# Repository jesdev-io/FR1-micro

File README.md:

# FR1-micro - Waveshare ESP32-S3-Touch-LCD-1.47 with libFRX

This project demonstrates using libFRX with the Waveshare ESP32-S3-Touch-LCD-1.47 board.

## Features

- **SD Card Access**: Write and read files using libFRX's SD card module
- **Audio Support**: Configured for the onboard MEMS microphone and DAC
- **I2C Support**: Ready for I2C device communication
- **jescore Integration**: Full command-line interface support

## Setup

### Prerequisites

1. Install PlatformIO
2. Clone this repository
3. Ensure libFRX is accessible (configured as a git dependency)

### Building and Uploading

```bash
cd FR1-micro
pio run -t upload
```

### Monitoring

```bash
pio device monitor
```

## Demo Program

The demo in `src/main.cpp` shows basic libFRX SD card operations:
- Initialize jescore and SD card
- Create/write/read/delete files
- List directory contents
- Proper error handling and cleanup

## Configuration

See `PIN_DEFS.md` for detailed pin definitions and `platformio.ini` for build configuration.

## Board Specifications

- **MCU**: ESP32-S3
- **Flash**: 16MB
- **PSRAM**: 8MB
- **Display**: 1.47" 172x320 RGB LCD with touch
- **SD Card**: SDMMC interface
- **Audio**: MEMS microphone + DAC
- **Connectivity**: WiFi + Bluetooth 5.0

## Troubleshooting

- **SD Card**: Ensure proper insertion, FAT32 format, check connections
- **Audio**: Verify I2S connections and sample rate settings
- **Compilation**: Check `platformio.ini` for correct module enables and pin definitions

## License

This project is licensed under the MIT License. See the LICENSE file for details.

## Contributing

Contributions are welcome! Please open issues or pull requests for any improvements or bug fixes.

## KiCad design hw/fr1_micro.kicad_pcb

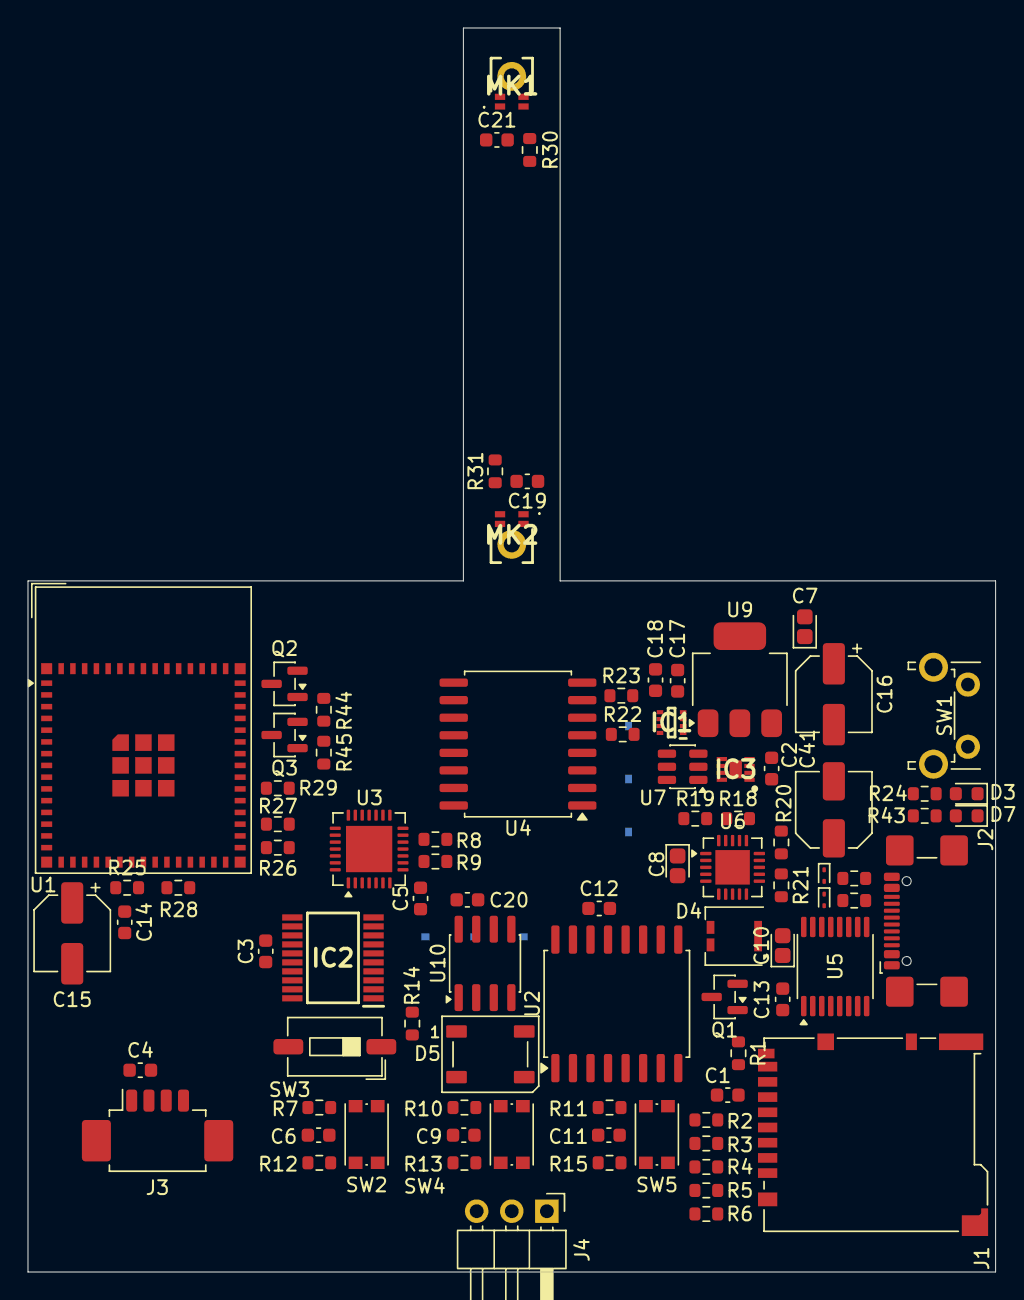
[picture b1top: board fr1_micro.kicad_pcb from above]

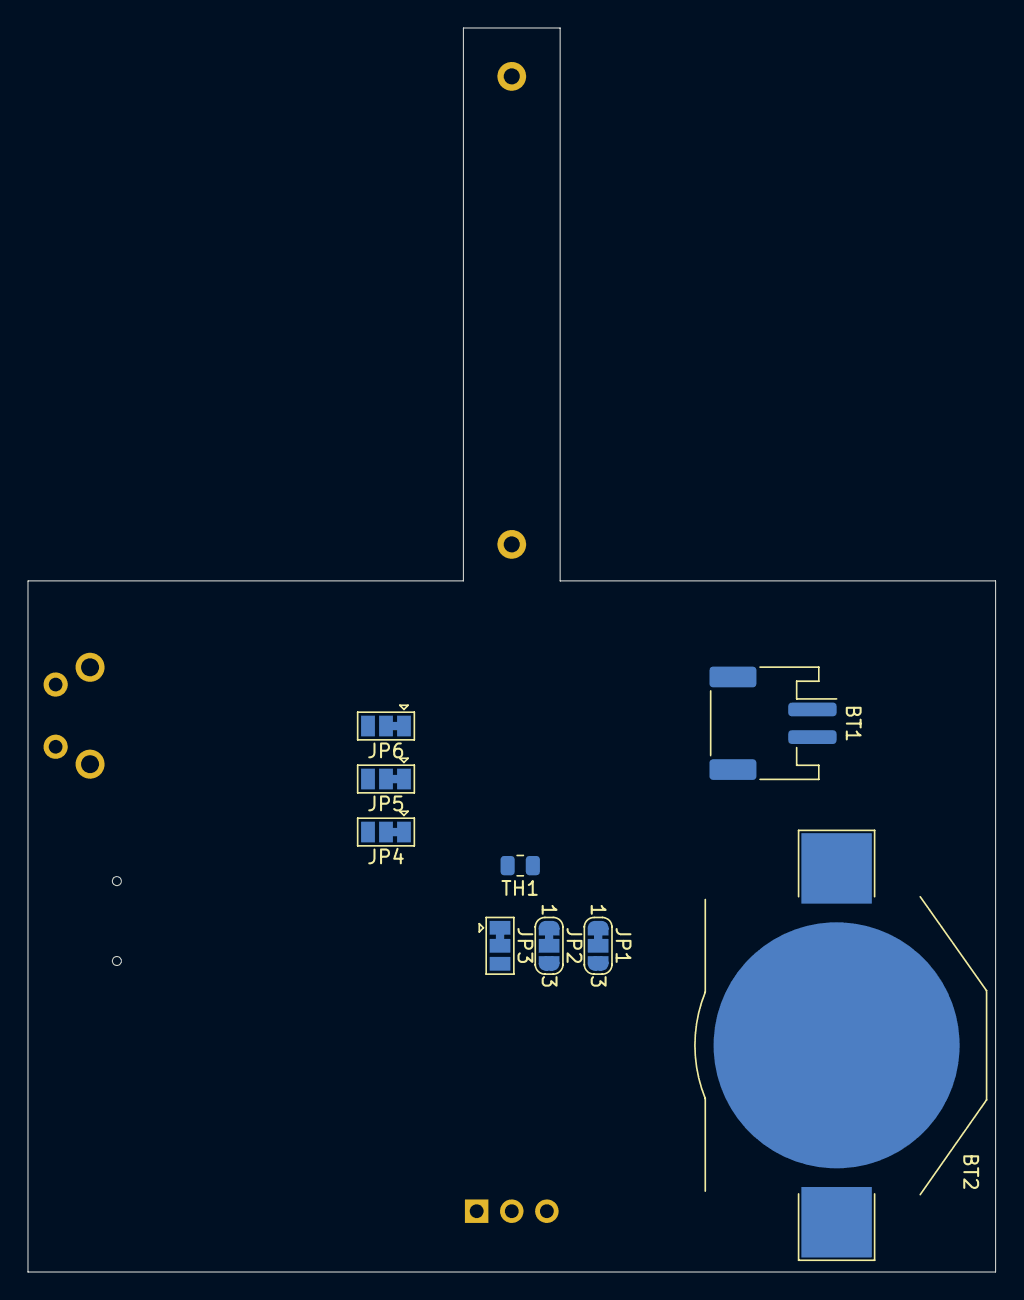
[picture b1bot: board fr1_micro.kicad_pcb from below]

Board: 4 copper layers, 70.0 x 90.0 mm, 97 parts (9 on the bottom side), 74 nets, no tracks yet.

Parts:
BT1: Battery_Cell; JST_PH_S2B-PH-SM4-TB_1x02-1MP_P2.00mm_Horizontal
BT2: Battery_Cell; BatteryHolder_Keystone_3002_1x2032
C1, C2, C3, C4, C5, C6, C9, C11, C12, C14, C19, C20, C21: 100n; C_0603_1608Metric
C7: 22u; CP_EIA-1608-08_AVX-J
C8: 4u7; CP_EIA-1608-08_AVX-J
C10: 10u; CP_EIA-1608-08_AVX-J
C13: 1µ; C_0603_1608Metric
C15: 47u; CP_Elec_5x5.4
C16: 4µ7; CP_Elec_5x5.4
C17: 100p; C_0603_1608Metric
C18: 6.8nF; C_0603_1608Metric
C41: 4u7; C_Elec_5x5.4
D1, D2: ESD9B3.3ST5G; D_SOD-923
D3: RED; D_0603_1608Metric
D4: ZEN056V230A16LS; Littelfuse_PolyZen-LS
D5: WS2812B; LED_WS2812B_PLCC4_5.0x5.0mm_P3.2mm
D7: GREEN; D_0603_1608Metric
IC1: TPS3424A11C13ADRLR; SOTFL50P160X60-8N
IC2: ADG5434BRUZ; SOP65P640X120-20N
IC3: MAX17048G+T10; SON50P200X200X80-9N-D
J1: Micro_SD_Card_Det1; microSD_HC_Hirose_DM3BT-DSF-PEJS
J2: USB_C_Receptacle; USB_C_Receptacle_GCT_USB4110
J3: Conn_01x04_Pin; Molex_PicoBlade_53261-0471_1x04-1MP_P1.25mm_Horizontal
J4: Conn_01x03_Pin; PinHeader_1x03_P2.54mm_Horizontal
JP1, JP2: SolderJumper_3_Bridged12; SolderJumper-3_P1.3mm_Bridged12_RoundedPad1.0x1.5mm_NumberL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
JP3, JP4, JP5, JP6: SolderJumper_3_Bridged12; SolderJumper-3_P1.3mm_Bridged12_Pad1.0x1.5mm
MK1, MK2: IM72D128V01XTMA1
Q1: AO3400A; SOT-23
Q2, Q3: BC847; SOT-23
R1, R2, R3, R4, R5, R6, R7, R8, R10, R11, R14, R22, R23, R44, R45: 10k; R_0603_1608Metric
R9: 1k; R_0603_1608Metric
R12, R13, R15: 100; R_0603_1608Metric
R16, R17: 5k1; R_0603_1608Metric
R18: 330k; R_0603_1608Metric
R19: 110k; R_0603_1608Metric
R20: 2k; R_0603_1608Metric
R21: 20k; R_0603_1608Metric
R24, R43: 470; R_0603_1608Metric
R25, R26, R27, R30, R31: 63; R_0603_1608Metric
R28, R29: 4k7; R_0603_1608Metric
SW1: SW_Push; SW_Tactile_SPST_Angled_PTS645Vx31-2LFS
SW2, SW4, SW5: SW_Push; SW_Push_1P1T_NO_CK_KMR2
SW3: SW_DIP_x01; SW_DIP_SPSTx01_Slide_6.7x4.1mm_W6.73mm_P2.54mm_LowProfile_J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
TH1: Thermistor_NTC 10k; R_0805_2012Metric
U1: ESP32-S3-MINI-1; ESP32-S2-MINI-1
U2: DS3231M; SOIC-16W_7.5x10.3mm_P1.27mm
U3: CP2102N-Axx-xQFN28; QFN-28-1EP_5x5mm_P0.5mm_EP3.35x3.35mm
U4: PCF8574AT; SOIC-16W_7.5x10.3mm_P1.27mm
U5: IP2721; TSSOP-16_4.4x5mm_P0.65mm
U6: MCP73871; QFN-20-1EP_4x4mm_P0.5mm_EP2.5x2.5mm
U7: TPS22917DBV; SOT-23-6
U9: AMS1117-3.3; SOT-223-3_TabPin2
U10: 24LC256; SOIC-8_3.9x4.9mm_P1.27mm

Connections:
+3.3V: C1.1, C3.1, C4.1, C5.2, C7.1, C14.1, C15.1, C19.1, C20.1, C21.1, C41.1, D5.1 (VDD), IC2.16 (VDD), J1.4 (VDD), J3.1, JP1.1 (A), JP2.1 (A), JP3.1 (A), JP4.1 (A), JP5.1 (A), JP6.1 (A), MK1.2 (VDD), MK2.2 (VDD), MK2.4 (SELECT), R1.1, R2.1, R3.1, R4.1, R5.1, R6.1, R7.2, R9.1, R10.2, R11.2, R14.2, R22.2, R23.2, R28.2, R29.2, U1.3 (3V3), U2.2 (VCC), U3.6 (VDD), U3.7 (VREGIN), U4.16 (VDD), U9.2 (VO), U10.8 (VCC)
/comms/DTR: Q3.2 (E), R44.1, U3.28 (~DTR)
/comms/RTS: Q2.2 (E), R45.1, U3.24 (~RTS)
/comms/USB_UART_D+: IC2.2 (S1A), J4.1, U3.4 (D+)
/comms/USB_UART_D-: IC2.9 (S2A), J4.2, U3.5 (D-)
/power/5V_ON: C8.1, IC1.3 (VDD), U6.1 (OUT), U6.20 (OUT), U7.1 (VIN)
/power/5V_PD: D4.3 (VOUT), R18.2, R24.1, R43.1, U6.4 (PROG2), U6.17 (CE), U6.18 (IN), U6.19 (IN)
/power/SWITCH_PIN: IC1.1 (PB), SW1.1
/power/TH: TH1.1, U6.5 (THERM)
/power/VBATT: BT1.1 (+), C2.1, C16.2, IC3.2 (CELL), IC3.3 (VDD), U6.14 (V_{BAT}), U6.15 (V_{BAT}), U6.16 (V_{BAT_SENSE})
BOOT: Q3.3 (C), U1.4 (IO0)
CC1: J2.A5 (CC1), R16.2, U5.13 (CC1)
CC2: J2.B5 (CC2), R17.2, U5.12 (CC2)
COMMS_UART_RX: U1.39 (TXD0), U3.25 (RXD)
COMMS_UART_TX: U1.40 (RXD0), U3.26 (TXD)
EN: Q2.3 (C), U1.45 (EN)
GNDD: BT1.2 (-), BT2.2 (-), C1.2, C2.2, C3.2, C4.2, C5.1, C6.2, C7.2, C8.2, C9.2, C10.2, C11.2, C12.2, C13.1, C14.2, C15.2, C16.1, C17.1, C18.1, C19.2, C20.2, C21.2, C41.2, D1.1 (A1), D2.1 (A1), D4.2 (GND), D5.3 (VSS), IC1.2 (GND), IC2.5 (VSS), IC2.6 (GND), IC2.11 (IN3), IC2.12 (S3A), IC2.13 (D3), IC2.14 (S3B), IC2.17 (S4B), IC2.18 (D4), IC2.19 (S4A), IC2.20 (IN4), IC3.1 (CTG), IC3.4 (GND), IC3.6 (QSTRT), IC3.9 (EP), J1.6 (VSS), J1.10 (SHIELD), J2.A1 (GND), J2.A12 (GND), J2.B1 (GND), J2.B12 (GND), J3.2, J4.3, JP1.3 (B), JP2.3 (B), JP3.3 (B), JP4.3 (B), JP5.3 (B), JP6.3 (B), MK1.4 (SELECT), MK1.5 (GND), MK2.5 (GND), R8.2, R16.1, R17.1, R19.1, R20.2, R21.2, SW1.2, SW2.1, SW3.2, SW4.1, SW5.1, TH1.2, U1.1 (GND), U1.2 (GND), U1.42 (GND), U1.43 (GND), U1.46 (GND), U1.47 (GND), U1.48 (GND), U1.49 (GND), U1.50 (GND), U1.51 (GND), U1.52 (GND), U1.53 (GND), U1.54 (GND), U1.55 (GND), U1.56 (GND), U1.57 (GND), U1.58 (GND), U1.59 (GND), U1.60 (GND), U1.61 (GND), U1.62 (GND), U1.63 (GND), U1.64 (GND), U1.65 (GND), U2.5 (GND), U2.6 (GND), U2.7 (GND), U2.8 (GND), U2.9 (GND), U2.10 (GND), U2.11 (GND), U2.12 (GND), U2.13 (GND), U3.3 (GND), U3.29 (GND), U4.8 (GND), U5.5 (GND), U5.11 (SEL), U6.3 (SEL), U6.9 (~TE), U6.10 (V_{SS}), U6.11 (V_{SS}), U6.21 (V_{SS}), U7.2 (GND), U9.1 (GND), U10.4 (GND), U10.7 (WP)
HW_USB_D+: D1.2 (A2), IC2.3 (D1), J2.A6 (D+), J2.B6 (D+)
HW_USB_D-: D2.2 (A2), IC2.8 (D2), J2.A7 (D-), J2.B7 (D-)
I2C_CLK: IC3.7 (SCL), J3.4, R28.1, U1.25 (IO21), U2.16 (SCL), U4.14 (SCL), U10.6 (SCL)
I2C_SDA: IC3.8 (SDA), J3.3, R29.1, U1.36 (IO40), U2.15 (SDA), U4.15 (SDA), U10.5 (SDA)
KILL: IC1.8 (KILL), R23.1, U4.7 (P3)
LED_NEOP: D5.4 (DIN), U1.27 (IO47)
unnamed: BT2.1 (+), C12.1, U2.14 (VBAT)
unnamed: D3.2 (A), R24.2
unnamed: D3.1 (K), U6.7 (STAT2)
unnamed: C10.1, D4.1 (VIN), Q1.2 (S), U5.16 (VBUS)
unnamed: D7.2 (A), R43.2
unnamed: D7.1 (K), U6.6 (~PG)
unnamed: C18.2, IC1.5 (LPT)
unnamed: IC1.6 (RESET_/~RESET), U7.3 (ON)
unnamed: C17.2, IC1.4 (SPT)
unnamed: JP1.2 (C), U10.1 (A0)
unnamed: JP2.2 (C), U10.2 (A1)
unnamed: JP3.2 (C), U10.3 (A2)
unnamed: JP4.2 (C), U4.1 (A0)
unnamed: JP5.2 (C), U4.2 (A1)
unnamed: JP6.2 (C), U4.3 (A2)
unnamed: MK1.1 (DATA), R30.2
unnamed: MK2.1 (DATA), R31.2
unnamed: Q1.1 (G), U5.1 (VBUSG)
unnamed: Q2.1 (B), R44.2
unnamed: Q3.1 (B), R45.2
unnamed: R10.1, R13.2, SW4.2
unnamed: R11.1, R15.2, SW5.2
unnamed: R7.1, R12.2, SW2.2
unnamed: R25.1, U1.19 (IO15)
unnamed: R26.1, U1.31 (IO35)
unnamed: R27.1, U1.32 (IO36)
unnamed: R9.2, U3.9 (~RST)
unnamed: R8.1, U3.11 (~SUSPEND)
unnamed: R20.1, U6.13 (PROG1)
unnamed: R21.1, U6.12 (PROG3)
unnamed: R18.1, R19.2, U6.2 (VPCC)
unnamed: U7.6 (VOUT), U9.3 (VI)
PDM_CLK: MK1.3 (CLOCK), MK2.3 (CLOCK), R25.2
PDM_DATA: R30.1, R31.1, U1.20 (IO16)
SDMMC_CLK: J1.5 (CLK), R3.2, R27.2
SDMMC_CMD: J1.3 (CMD), R4.2, R26.2
SDMMC_DAT0: J1.7 (DAT0), R2.2, U1.33 (IO37)
SDMMC_DAT1: J1.8 (DAT1), R1.2, U1.34 (IO38)
SDMMC_DAT2: J1.1 (DAT2), R6.2, U1.41 (IO45)
SDMMC_DAT3: J1.2 (DAT3/CD), R5.2, U1.35 (IO39)
SD_DETECT: J1.9 (DET), U4.4 (P0)
SEL_USB: IC2.1 (IN1), IC2.10 (IN2), R14.1, SW3.1, U4.12 (P7)
STAT1: U4.6 (P2), U6.8 (STAT1/~LBO)
SW1: C6.1, R12.1, U4.9 (P4)
SW2: C9.1, R13.1, U4.10 (P5)
SW3: C11.1, R15.1, U4.11 (P6)
UI_INT: U1.44 (IO46), U4.13 (~INT)
USB_D+: IC2.4 (S1B), U1.24 (USB_D+)
USB_D-: IC2.7 (S2B), U1.23 (USB_D-)
VBUS: C13.2, J2.A4 (VBUS), J2.A9 (VBUS), J2.B4 (VBUS), J2.B9 (VBUS), Q1.3 (D), U5.2 (VIN)
nINT: IC1.7 (~INT), R22.1, U4.5 (P1)
